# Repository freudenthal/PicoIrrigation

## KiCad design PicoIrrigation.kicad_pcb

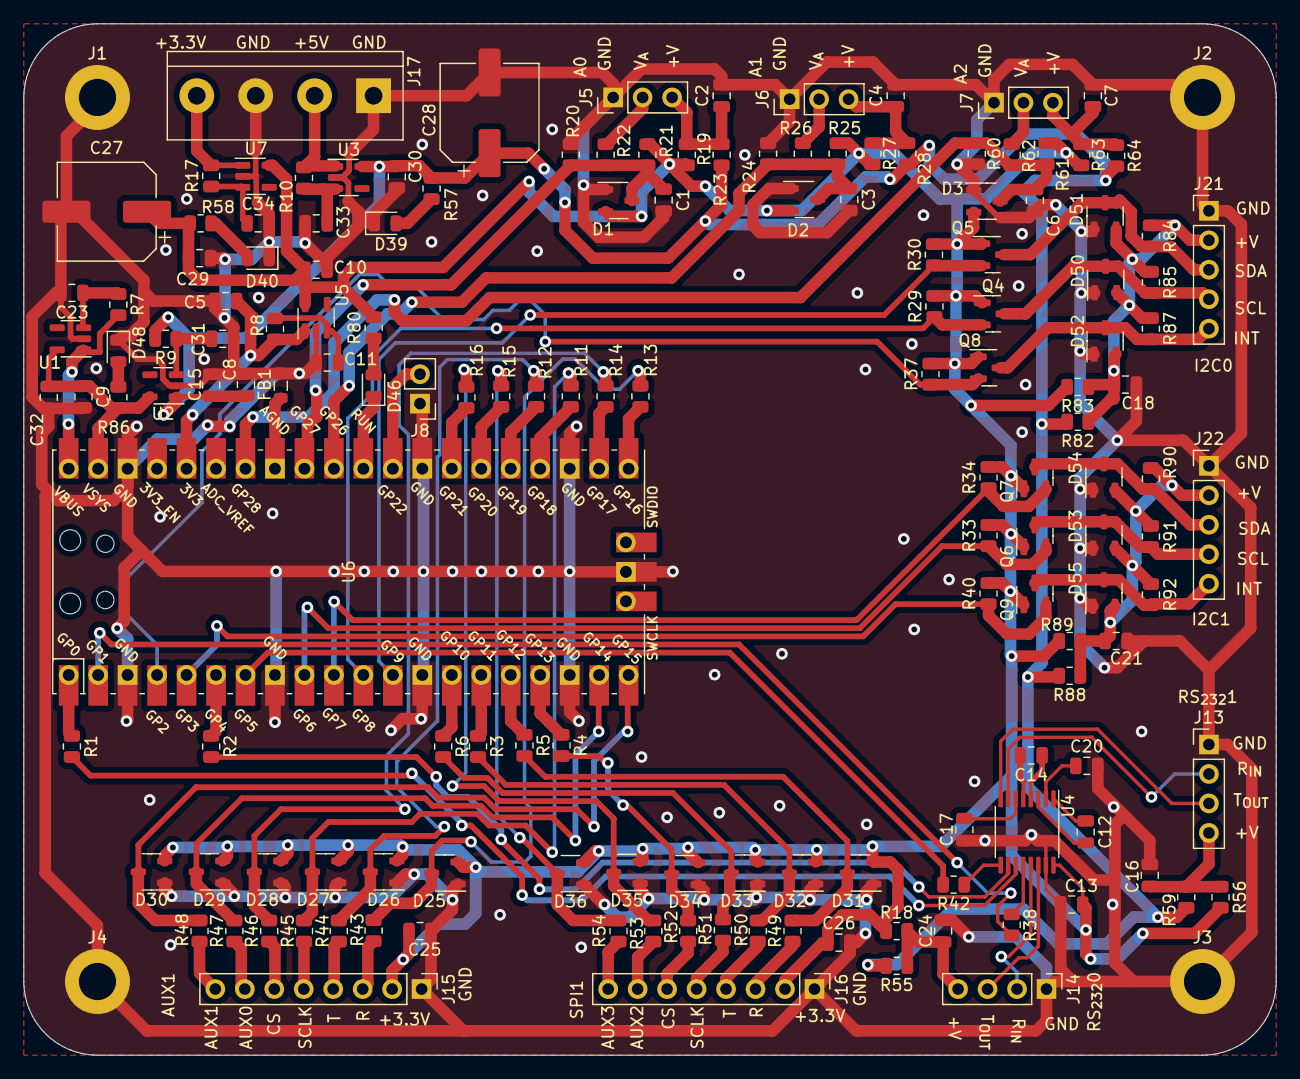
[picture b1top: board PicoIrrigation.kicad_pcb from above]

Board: 2 copper layers, 108.0 x 88.9 mm, 156 parts (0 on the bottom side), 97 nets.

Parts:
C1, C2, C3, C4, C6, C7, C8, C9, C11, C12, C13, C14, C17, C18, C20, C21, C23, C25, C26, C29, C30, C31, C33, C34: 1uF; C_0805_2012Metric
C5, C10, C15, C16, C24, C32: 10uF; C_0805_2012Metric
C27, C28: 100uF; CP_Elec_8x11.9
D1, D2, D3, D25, D26, D27, D28, D29, D30, D31, D32, D33, D34, D35, D36, D50, D51, D52, D53, D54, D55: 100V; SOT-23-3
D39, D40, D46, D48: LED; LED_0805_2012Metric
FB1: NS_Ferrite; L_0805_2012Metric
J1, J2, J3, J4: M3; MountingHole_3.2mm_M3_DIN965_Pad
J5, J6, J7: ADC; PinHeader_1x03_P2.54mm_Vertical
J8: RUN; PinHeader_1x02_P2.54mm_Vertical
J13: RSS232Out; PinHeader_1x04_P2.54mm_Vertical
J14: RSS232In; PinHeader_1x04_P2.54mm_Vertical
J15, J16: SPI; PinHeader_1x08_P2.54mm_Vertical
J17: V_{IN}; TerminalBlock_bornier-4_P5.08mm
J21, J22: I2C; PinHeader_1x05_P2.54mm_Vertical
Q4, Q5, Q6, Q7, Q8, Q9: Q_NMOS_GSD; SOT-23
R1, R2, R3, R4, R5, R6, R11, R12, R13, R14, R15, R16, R38, R42, R57, R80, R86: 500Ω; R_0805_2012Metric
R7, R8, R9, R10, R17: 100kΩ; R_0805_2012Metric
R18, R20, R21, R23, R24, R25, R28, R55, R56, R59, R60, R61, R64: NSΩ; R_0805_2012Metric
R19, R27, R63, R82, R83, R88, R89: 0Ω; R_0805_2012Metric
R22, R26, R29, R30, R33, R34, R37, R40, R62, R84, R85, R87, R90, R91, R92: 10kΩ; R_0805_2012Metric
R43, R44, R45, R46, R47, R48, R49, R50, R51, R52, R53, R54: 50Ω; R_0805_2012Metric
R58: 330kΩ; R_0805_2012Metric
U1, U2, U3, U5, U7: MAX40200AUK; SOT-23-5
U4: MAX3232; TSSOP-16_4.4x5mm_P0.65mm
U6: Pico; RPi_Pico_SMD_TH

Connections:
+3.3V: C10.1, C13.1, C25.1, C26.1, C27.1, C29.1, D1.2 (K), D2.2 (K), D3.2 (K), D25.2 (K), D26.2 (K), D27.2 (K), D28.2 (K), D29.2 (K), D30.2 (K), D31.2 (K), D32.2 (K), D33.2 (K), D34.2 (K), D35.2 (K), D36.2 (K), J15.2, J16.2, Q4.1 (G), Q5.1 (G), Q6.1 (G), Q7.1 (G), Q8.1 (G), Q9.1 (G), R18.2, R19.1, R21.1, R25.1, R27.1, R29.2, R30.2, R33.2, R34.2, R37.2, R40.2, R56.2, R58.2, R61.1, R63.1, R80.2, R83.2, R89.2, U4.16 (VCC), U5.5 (OUT), U7.5 (OUT)
+5V: C8.1, C15.1, C28.1, C30.1, R9.2, R23.1, R28.1, R55.2, R57.2, R59.2, R64.1, R82.2, R88.2, U2.1 (VDD), U3.5 (OUT)
/AUX0: D29.3 (A), R47.2, U6.19 (GPIO14)
/AUX1: D30.3 (A), R48.2, U6.20 (GPIO15)
/AUX2: D35.3 (A), R16.2, R53.2
/AUX3: D36.3 (A), R15.2, R54.2
/AnaloguePin1/V_{A}: C3.1, D2.3 (A), R24.1, R25.2, R26.2, U6.31 (GPIO26_ADC0)
/AnaloguePin2/V_{A}: C6.1, D3.3 (A), R60.1, R61.2, R62.2, U6.34 (GPIO28_ADC2)
/AnaloguePin/V_{A}: C1.1, D1.3 (A), R20.1, R21.2, R22.2, U6.32 (GPIO27_ADC1)
/CS0: D28.3 (A), R14.2, R46.2
/CS1: D34.3 (A), R4.2, R52.2
/I2CConnector0/INT: Q8.2 (S), R37.1, U6.4 (GPIO2)
/I2CConnector0/SCL: Q4.2 (S), R29.1, U6.11 (GPIO8)
/I2CConnector0/SDA: Q5.2 (S), R30.1, U6.12 (GPIO9)
/I2CConnector0/VI2C: C18.1, D50.2 (K), D51.2 (K), D52.2 (K), J21.2, R82.1, R83.1, R84.1, R85.1, R87.1
/I2CConnector1/INT: Q9.2 (S), R40.1, U6.5 (GPIO3)
/I2CConnector1/SCL: Q6.2 (S), R33.1, U6.9 (GPIO6)
/I2CConnector1/SDA: Q7.2 (S), R34.1, U6.10 (GPIO7)
/I2CConnector1/VI2C: C21.1, D53.2 (K), D54.2 (K), D55.2 (K), J22.2, R88.1, R89.1, R90.1, R91.1, R92.1
/RX0: R38.2, U6.2 (GPIO1)
/RX1: R42.2, U6.7 (GPIO5)
/SCLK0: D27.3 (A), R11.2, R45.2
/SCLK1: D33.3 (A), R6.2, R51.2
/SPI_{Rx}0: D25.3 (A), R13.2, R43.2
/SPI_{Rx}1: D31.3 (A), R5.2, R49.2
/SPI_{Tx}0: D26.3 (A), R12.2, R44.2
/SPI_{Tx}1: D32.3 (A), R3.2, R50.2
/TX0: R1.2, U4.11 (T1IN)
/TX1: R2.2, U4.10 (T2IN)
GND: C1.2, C2.2, C3.2, C4.2, C5.2, C6.2, C7.2, C8.2, C9.2, C10.2, C11.2, C13.2, C15.2, C16.2, C17.2, C18.2, C20.2, C21.2, C23.2, C24.2, C25.2, C26.2, C27.2, C28.2, C29.2, C30.2, C31.2, C32.2, C33.2, C34.2, D1.1 (K), D2.1 (K), D3.1 (K), D25.1 (K), D26.1 (K), D27.1 (K), D28.1 (K), D29.1 (K), D30.1 (K), D31.1 (K), D32.1 (K), D33.1 (K), D34.1 (K), D35.1 (K), D36.1 (K), D39.1 (K), D40.1 (K), D48.1 (K), D50.1 (K), D51.1 (K), D52.1 (K), D53.1 (K), D54.1 (K), D55.1 (K), FB1.1, J1.1, J2.1, J3.1, J4.1, J5.1, J6.1, J7.1, J8.1, J13.1, J14.1, J15.1, J16.1, J17.1, J17.3, J21.1, J22.1, R20.2, R24.2, R60.2, U1.2 (GND), U2.2 (GND), U3.2 (GND), U4.15 (GND), U5.2 (GND), U6.3 (GND), U6.8 (GND), U6.13 (GND), U6.18 (GND), U6.23 (GND), U6.28 (GND), U6.38 (GND), U6.42 (GND), U7.2 (GND)
unnamed: D39.2 (A), R57.1
unnamed: D40.2 (A), R58.1
unnamed: D46.2 (A), R80.1
unnamed: D46.1 (K), U6.30 (RUN)
unnamed: D48.2 (A), R86.1
unnamed: D50.3 (A), J21.4, Q4.3 (D), R85.2
unnamed: D51.3 (A), J21.3, Q5.3 (D), R84.2
unnamed: D52.3 (A), J21.5, Q8.3 (D), R87.2
unnamed: D53.3 (A), J22.4, Q6.3 (D), R91.2
unnamed: D54.3 (A), J22.3, Q7.3 (D), R90.2
unnamed: D55.3 (A), J22.5, Q9.3 (D), R92.2
unnamed: J5.2, R22.1
unnamed: C2.1, J5.3, R19.2, R23.2
unnamed: J6.2, R26.1
unnamed: C4.1, J6.3, R27.2, R28.2
unnamed: J7.2, R62.1
unnamed: C7.1, J7.3, R63.2, R64.2
unnamed: J8.2, U6.29 (GPIO22)
unnamed: J13.2, U4.7 (T2OUT)
unnamed: J13.3, U4.8 (R2IN)
unnamed: C16.1, J13.4, R56.1, R59.1
unnamed: J14.2, U4.13 (R1IN)
unnamed: J14.3, U4.14 (T1OUT)
unnamed: C24.1, J14.4, R18.1, R55.1
unnamed: J15.3, R43.1
unnamed: J15.4, R44.1
unnamed: J15.5, R45.1
unnamed: J15.6, R46.1
unnamed: J15.7, R47.1
unnamed: J15.8, R48.1
unnamed: J16.3, R49.1
unnamed: J16.4, R50.1
unnamed: J16.5, R51.1
unnamed: J16.6, R52.1
unnamed: J16.7, R53.1
unnamed: J16.8, R54.1
unnamed: J17.2, R10.2, U3.1 (VDD)
unnamed: J17.4, R17.2, U7.1 (VDD)
unnamed: C23.1, R7.1, U1.3 (EN)
unnamed: C9.1, C32.1, R86.2, U1.5 (OUT), U2.5 (OUT), U6.39 (VSYS)
unnamed: R7.2, U1.1 (VDD), U6.40 (VBUS)
unnamed: C31.1, R9.1, U2.3 (EN)
unnamed: C33.1, R10.1, U3.3 (EN)
unnamed: C12.1, U4.1 (C1+)
unnamed: C12.2, U4.3 (C1-)
unnamed: C14.1, U4.4 (C2+)
unnamed: C14.2, U4.5 (C2-)
unnamed: R38.1, U4.12 (R1OUT)
unnamed: R42.1, U4.9 (R2OUT)
unnamed: C20.1, U4.2 (VS+)
unnamed: C17.1, U4.6 (VS-)
unnamed: C11.1, R8.1, U5.3 (EN)
unnamed: C5.1, R8.2, U5.1 (VDD), U6.36 (3V3)
unnamed: FB1.2, U6.33 (AGND)
unnamed: R1.1, U6.1 (GPIO0)
unnamed: R2.1, U6.6 (GPIO4)
unnamed: R6.1, U6.14 (GPIO10)
unnamed: R3.1, U6.15 (GPIO11)
unnamed: R5.1, U6.16 (GPIO12)
unnamed: R4.1, U6.17 (GPIO13)
unnamed: R13.1, U6.21 (GPIO16)
unnamed: R14.1, U6.22 (GPIO17)
unnamed: R11.1, U6.24 (GPIO18)
unnamed: R12.1, U6.25 (GPIO19)
unnamed: R15.1, U6.26 (GPIO20)
unnamed: R16.1, U6.27 (GPIO21)
unnamed: C34.1, R17.1, U7.3 (EN)

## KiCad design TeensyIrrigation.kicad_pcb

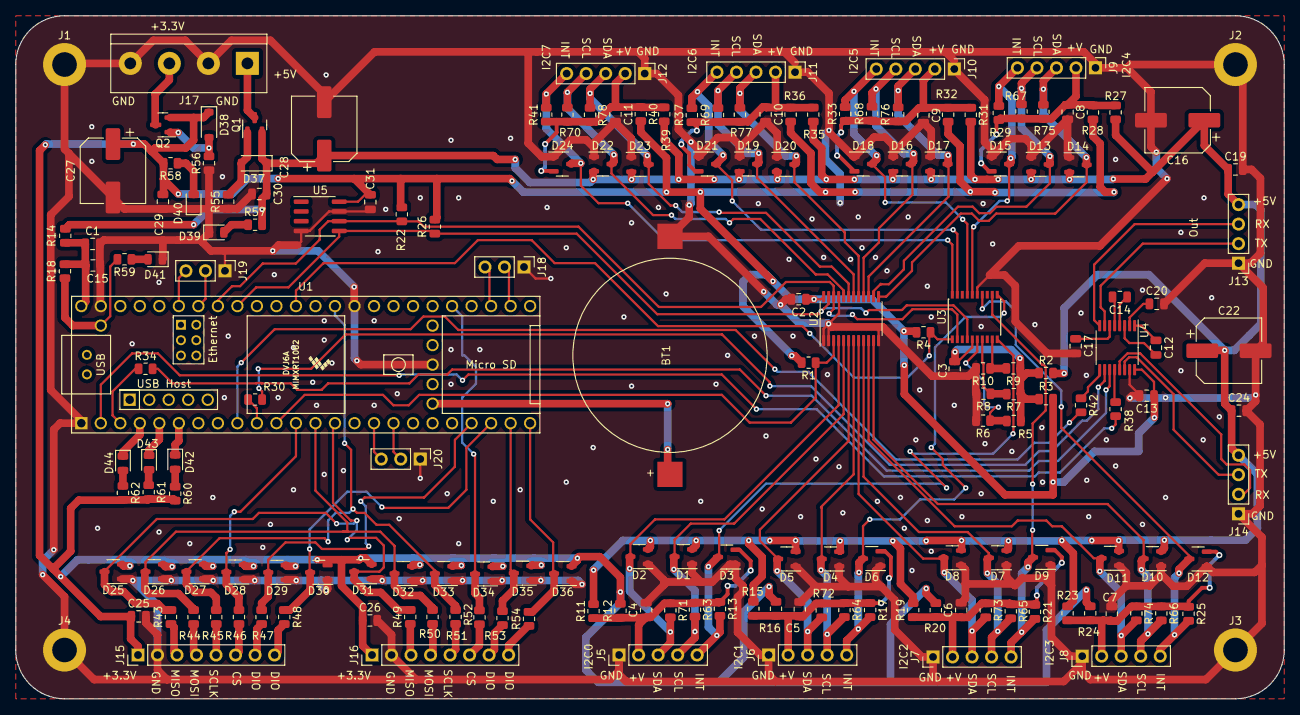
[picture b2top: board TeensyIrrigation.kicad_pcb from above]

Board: 2 copper layers, 165.1 x 88.9 mm, 178 parts (0 on the bottom side), 104 nets.

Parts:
BT1: 2032Coin; BC2032
C1, C2, C3, C4, C5, C6, C7, C8, C9, C10, C11, C12, C13, C14, C17, C19, C20, C24, C25, C26, C29, C30, C31: 1uF; C_0805_2012Metric
C15: 10uF; C_0805_2012Metric
C16, C22, C27, C28: 100uF; CP_Elec_8x11.9
D1, D2, D3, D4, D5, D6, D7, D8, D9, D10, D11, D12, D13, D14, D15, D16, D17, D18, D19, D20, D21, D22, D23, D24, D25, D26, D27, D28, D29, D30, D31, D32, D33, D34, D35, D36: 100V; SOT-23-3
D37, D38: 10V; D_SOD-123
D39, D40, D41, D42, D43, D44: LED; LED_0805_2012Metric
J1, J2, J3, J4: M3; MountingHole_3.2mm_M3_DIN965_Pad
J5, J6, J7, J8, J9, J10, J11, J12: I2C; PinHeader_1x05_P2.54mm_Vertical
J13: RSS232Out; PinHeader_1x04_P2.54mm_Vertical
J14: RSS232In; PinHeader_1x04_P2.54mm_Vertical
J15, J16: SPI; PinHeader_1x08_P2.54mm_Vertical
J17: V_{IN}; TerminalBlock_bornier-4_P5.08mm
J18: UART8; PinHeader_1x03_P2.54mm_Vertical
J19: UART5; PinHeader_1x03_P2.54mm_Vertical
J20: UART6; PinHeader_1x03_P2.54mm_Vertical
Q1, Q2: Q_PMOS_GSD; SOT-23
R1, R4, R5, R6, R7, R8, R9, R10, R13, R17, R21, R22, R25, R26, R29, R33, R37, R41, R63, R64, R65, R66, R67, R68, R69, R70, R71, R72, R73, R74, R75, R76, R77, R78: 10kΩ; R_0805_2012Metric
R2, R3, R11, R12, R14, R15, R16, R18, R19, R20, R23, R24, R27, R28, R31, R32, R35, R36, R39, R40: 0Ω; R_0805_2012Metric
R30, R34, R38, R42, R57, R59, R60, R61, R62: 500Ω; R_0805_2012Metric
R43, R44, R45, R46, R47, R48, R49, R50, R51, R52, R53, R54: 50Ω; R_0805_2012Metric
R55, R56: 100kΩ; R_0805_2012Metric
R58: 330kΩ; R_0805_2012Metric
U1: Teensy4.1; Teensy41
U2: TCA9548APWR; TSSOP-24_4.4x7.8mm_P0.65mm
U3: PCF8574TS; SSOP-20_4.4x6.5mm_P0.65mm
U4: MAX3232; TSSOP-16_4.4x5mm_P0.65mm
U5: FM24CL16B; SOIC-8_3.9x4.9mm_P1.27mm

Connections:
+3.3V: C2.1, C13.1, C25.1, C26.1, C27.1, C29.1, C31.1, D25.2 (K), D26.2 (K), D27.2 (K), D28.2 (K), D29.2 (K), D30.2 (K), D31.2 (K), D32.2 (K), D33.2 (K), D34.2 (K), D35.2 (K), D36.2 (K), D38.1 (K), J15.1, J16.1, Q2.2 (S), R1.2, R3.2, R4.2, R12.2, R16.2, R20.2, R22.2, R24.2, R26.2, R28.2, R32.2, R36.2, R40.2, R58.2, R60.2, R61.2, R62.2, U2.24 (VCC), U4.16 (VCC), U5.8 (VDD)
+5V: C16.1, C19.1, C22.1, C24.1, C28.1, C30.1, D1.2 (K), D2.2 (K), D4.2 (K), D5.2 (K), D7.2 (K), D8.2 (K), D10.2 (K), D11.2 (K), D13.2 (K), D14.2 (K), D16.2 (K), D17.2 (K), D19.2 (K), D20.2 (K), D22.2 (K), D23.2 (K), D37.1 (K), J13.4, J14.4, Q1.2 (S), R2.2, R11.2, R14.1, R15.2, R19.2, R23.2, R27.2, R31.2, R35.2, R39.2, R57.2
+BATT: BT1.1 (+), U1.50 (VBAT)
/AUX0: D29.3 (A), R47.2, U1.21 (29_TX7)
/AUX1: D30.3 (A), R48.2, U1.22 (30_CRX3)
/AUX2: D35.3 (A), R53.2, U1.23 (31_CTX3)
/AUX3: D36.3 (A), R54.2, U1.24 (32_OUT1B)
/CS0: D28.3 (A), R46.2, U1.12 (10_CS_MQSR)
/CS1: D34.3 (A), R52.2, U1.29 (37_CS)
/MISO: D25.3 (A), D31.3 (A), R43.2, R49.2, U1.14 (12_MISO_MQSL)
/MOSI: D26.3 (A), D32.3 (A), R44.2, R50.2, U1.13 (11_MOSI_CTX1)
/RX0: R38.2, U1.2 (0_RX1_CRX2_CS1)
/RX1: R42.2, U1.9 (7_RX2_OUT1A)
/SCL: R22.1, U1.41 (19_A5_SCL), U2.22 (SCL), U3.2 (SCL), U5.6 (SCL)
/SCLK: D27.3 (A), D33.3 (A), R45.2, R51.2, U1.35 (13_SCK_LED)
/SDA: R26.1, U1.40 (18_A4_SDA), U2.23 (SDA), U3.4 (SDA), U5.5 (SDA)
/TCA9548AI2CMultiplexer/I2CConnector1/INT: D6.3 (A), J6.5, R17.2, U3.11 (P1)
/TCA9548AI2CMultiplexer/I2CConnector1/SCL: D4.3 (A), J6.4, R64.2, U2.7 (SC1)
/TCA9548AI2CMultiplexer/I2CConnector1/SDA: D5.3 (A), J6.3, R72.2, U2.6 (SD1)
/TCA9548AI2CMultiplexer/I2CConnector1/VBus: C5.1, D6.2 (K), J6.2, R15.1, R16.1, R17.1, R64.1, R72.1
/TCA9548AI2CMultiplexer/I2CConnector2/INT: D9.3 (A), J7.5, R21.2, U3.12 (P2)
/TCA9548AI2CMultiplexer/I2CConnector2/SCL: D7.3 (A), J7.4, R65.2, U2.9 (SC2)
/TCA9548AI2CMultiplexer/I2CConnector2/SDA: D8.3 (A), J7.3, R73.2, U2.8 (SD2)
/TCA9548AI2CMultiplexer/I2CConnector2/VBus: C6.1, D9.2 (K), J7.2, R19.1, R20.1, R21.1, R65.1, R73.1
/TCA9548AI2CMultiplexer/I2CConnector3/INT: D12.3 (A), J8.5, R25.2, U3.14 (P3)
/TCA9548AI2CMultiplexer/I2CConnector3/SCL: D10.3 (A), J8.4, R66.2, U2.11 (SC3)
/TCA9548AI2CMultiplexer/I2CConnector3/SDA: D11.3 (A), J8.3, R74.2, U2.10 (SD3)
/TCA9548AI2CMultiplexer/I2CConnector3/VBus: C7.1, D12.2 (K), J8.2, R23.1, R24.1, R25.1, R66.1, R74.1
/TCA9548AI2CMultiplexer/I2CConnector4/INT: D15.3 (A), J9.5, R29.2, U3.16 (P4)
/TCA9548AI2CMultiplexer/I2CConnector4/SCL: D13.3 (A), J9.4, R67.2, U2.14 (SC4)
/TCA9548AI2CMultiplexer/I2CConnector4/SDA: D14.3 (A), J9.3, R75.2, U2.13 (SD4)
/TCA9548AI2CMultiplexer/I2CConnector4/VBus: C8.1, D15.2 (K), J9.2, R27.1, R28.1, R29.1, R67.1, R75.1
/TCA9548AI2CMultiplexer/I2CConnector5/INT: D18.3 (A), J10.5, R33.2, U3.17 (P5)
/TCA9548AI2CMultiplexer/I2CConnector5/SCL: D16.3 (A), J10.4, R68.2, U2.16 (SC5)
/TCA9548AI2CMultiplexer/I2CConnector5/SDA: D17.3 (A), J10.3, R76.2, U2.15 (SD5)
/TCA9548AI2CMultiplexer/I2CConnector5/VBus: C9.1, D18.2 (K), J10.2, R31.1, R32.1, R33.1, R68.1, R76.1
/TCA9548AI2CMultiplexer/I2CConnector6/INT: D21.3 (A), J11.5, R37.2, U3.19 (P6)
/TCA9548AI2CMultiplexer/I2CConnector6/SCL: D19.3 (A), J11.4, R69.2, U2.18 (SC6)
/TCA9548AI2CMultiplexer/I2CConnector6/SDA: D20.3 (A), J11.3, R77.2, U2.17 (SD6)
/TCA9548AI2CMultiplexer/I2CConnector6/VBus: C10.1, D21.2 (K), J11.2, R35.1, R36.1, R37.1, R69.1, R77.1
/TCA9548AI2CMultiplexer/I2CConnector7/INT: D24.3 (A), J12.5, R41.2, U3.20 (P7)
/TCA9548AI2CMultiplexer/I2CConnector7/SCL: D22.3 (A), J12.4, R70.2, U2.20 (SC7)
/TCA9548AI2CMultiplexer/I2CConnector7/SDA: D23.3 (A), J12.3, R78.2, U2.19 (SD7)
/TCA9548AI2CMultiplexer/I2CConnector7/VBus: C11.1, D24.2 (K), J12.2, R39.1, R40.1, R41.1, R70.1, R78.1
/TCA9548AI2CMultiplexer/I2CConnector/INT: D3.3 (A), J5.5, R13.2, U3.10 (P0)
/TCA9548AI2CMultiplexer/I2CConnector/SCL: D1.3 (A), J5.4, R63.2, U2.5 (SC0)
/TCA9548AI2CMultiplexer/I2CConnector/SDA: D2.3 (A), J5.3, R71.2, U2.4 (SD0)
/TCA9548AI2CMultiplexer/I2CConnector/VBus: C4.1, D3.2 (K), J5.2, R11.1, R12.1, R13.1, R63.1, R71.1
/TCA9548AI2CMultiplexer/~INT: R4.1, U1.37 (15_A1_RX3_SPDIF_IN), U3.1 (~INT)
/TX0: R34.2, U4.11 (T1IN)
/TX1: R30.2, U4.10 (T2IN)
/~RESETI2C: R1.1, U1.11 (9_OUT1C), U2.3 (~RESET)
GND: BT1.2 (-), C1.2, C2.2, C3.2, C4.2, C5.2, C6.2, C7.2, C8.2, C9.2, C10.2, C11.2, C13.2, C15.2, C16.2, C17.2, C19.2, C20.2, C22.2, C24.2, C25.2, C26.2, C27.2, C28.2, C29.2, C30.2, C31.2, D1.1 (K), D2.1 (K), D3.1 (K), D4.1 (K), D5.1 (K), D6.1 (K), D7.1 (K), D8.1 (K), D9.1 (K), D10.1 (K), D11.1 (K), D12.1 (K), D13.1 (K), D14.1 (K), D15.1 (K), D16.1 (K), D17.1 (K), D18.1 (K), D19.1 (K), D20.1 (K), D21.1 (K), D22.1 (K), D23.1 (K), D24.1 (K), D25.1 (K), D26.1 (K), D27.1 (K), D28.1 (K), D29.1 (K), D30.1 (K), D31.1 (K), D32.1 (K), D33.1 (K), D34.1 (K), D35.1 (K), D36.1 (K), D39.1 (K), D40.1 (K), D41.1 (K), J1.1, J2.1, J3.1, J4.1, J5.1, J6.1, J7.1, J8.1, J9.1, J10.1, J11.1, J12.1, J13.1, J14.1, J15.2, J16.2, J17.2, J17.4, J18.1, J19.1, J20.1, R6.2, R8.2, R10.2, R55.1, R56.1, U1.1 (GND), U1.34 (GND), U1.47 (GND), U1.52 (GND), U2.1 (A0), U2.2 (A1), U2.12 (GND), U2.21 (A2), U3.15 (VSS), U4.15 (GND), U5.4 (VSS), U5.7 (WP)
unnamed: D37.2 (A), Q1.1 (G), R55.2
unnamed: D38.2 (A), Q2.1 (G), R56.2
unnamed: D39.2 (A), R57.1
unnamed: D40.2 (A), R58.1
unnamed: D41.2 (A), R59.1
unnamed: D42.2 (A), R60.1
unnamed: D42.1 (K), U1.6 (4_BCLK2)
unnamed: D43.2 (A), R61.1
unnamed: D43.1 (K), U1.5 (3_LRCLK2)
unnamed: D44.2 (A), R62.1
unnamed: D44.1 (K), U1.4 (2_OUT2)
unnamed: J13.2, U4.7 (T2OUT)
unnamed: J13.3, U4.8 (R2IN)
unnamed: J14.2, U4.13 (R1IN)
unnamed: J14.3, U4.14 (T1OUT)
unnamed: J15.3, R43.1
unnamed: J15.4, R44.1
unnamed: J15.5, R45.1
unnamed: J15.6, R46.1
unnamed: J15.7, R47.1
unnamed: J15.8, R48.1
unnamed: J16.3, R49.1
unnamed: J16.4, R50.1
unnamed: J16.5, R51.1
unnamed: J16.6, R52.1
unnamed: J16.7, R53.1
unnamed: J16.8, R54.1
unnamed: J17.1, Q1.3 (D)
unnamed: J17.3, Q2.3 (D)
unnamed: J18.2, U1.26 (34_RX8)
unnamed: J18.3, U1.27 (35_TX8)
unnamed: J19.2, U1.42 (20_A6_TX5_LRCLK1)
unnamed: J19.3, U1.43 (21_A7_RX5_BCLK1)
unnamed: J20.2, U1.17 (25_A11_RX6_SDA2)
unnamed: J20.3, U1.16 (24_A10_TX6_SCL2)
unnamed: R34.1, U1.3 (1_TX1_CTX2_MISO1)
unnamed: R30.1, U1.10 (8_TX2_IN1)
unnamed: C1.1, C15.1, R14.2, R18.1, U1.48 (VIN)
unnamed: R18.2, R59.2, U1.49 (VUSB)
unnamed: R5.2, R6.1, U3.6 (A0)
unnamed: R7.2, R8.1, U3.7 (A1)
unnamed: R9.2, R10.1, U3.9 (A2)
unnamed: C3.1, R2.1, R3.1, R5.1, R7.1, R9.1, U3.5 (VDD)
unnamed: C12.1, U4.1 (C1+)
unnamed: C12.2, U4.3 (C1-)
unnamed: C14.1, U4.4 (C2+)
unnamed: C14.2, U4.5 (C2-)
unnamed: R38.1, U4.12 (R1OUT)
unnamed: R42.1, U4.9 (R2OUT)
unnamed: C20.1, U4.2 (VS+)
unnamed: C17.1, U4.6 (VS-)

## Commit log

2023-12-28 Change from TeensyIrrigation to PicoIrrigation and change the connectors. Will use breakout board for I2C MUX if necessary.
2023-12-28 Remove battery.
2023-12-29 Finished schematic. Move to PCB.
2023-12-30 Finished layout
2024-01-08 Ready V1
2024-01-08 Remove junk files
